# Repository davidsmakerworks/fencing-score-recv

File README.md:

# fencing-score-recv
Remote fencing scoring light display receiver

This is the receiver portion of the [remote fencing scoring light display](https://github.com/davidsmakerworks/fencing-score-xmit) project. This is designed to be placed on the wall at the ends of the fencing strip. It includes a timer to automatically turn off the lights if no shutoff signal is received from the transmitter within a reasonable amount of time.

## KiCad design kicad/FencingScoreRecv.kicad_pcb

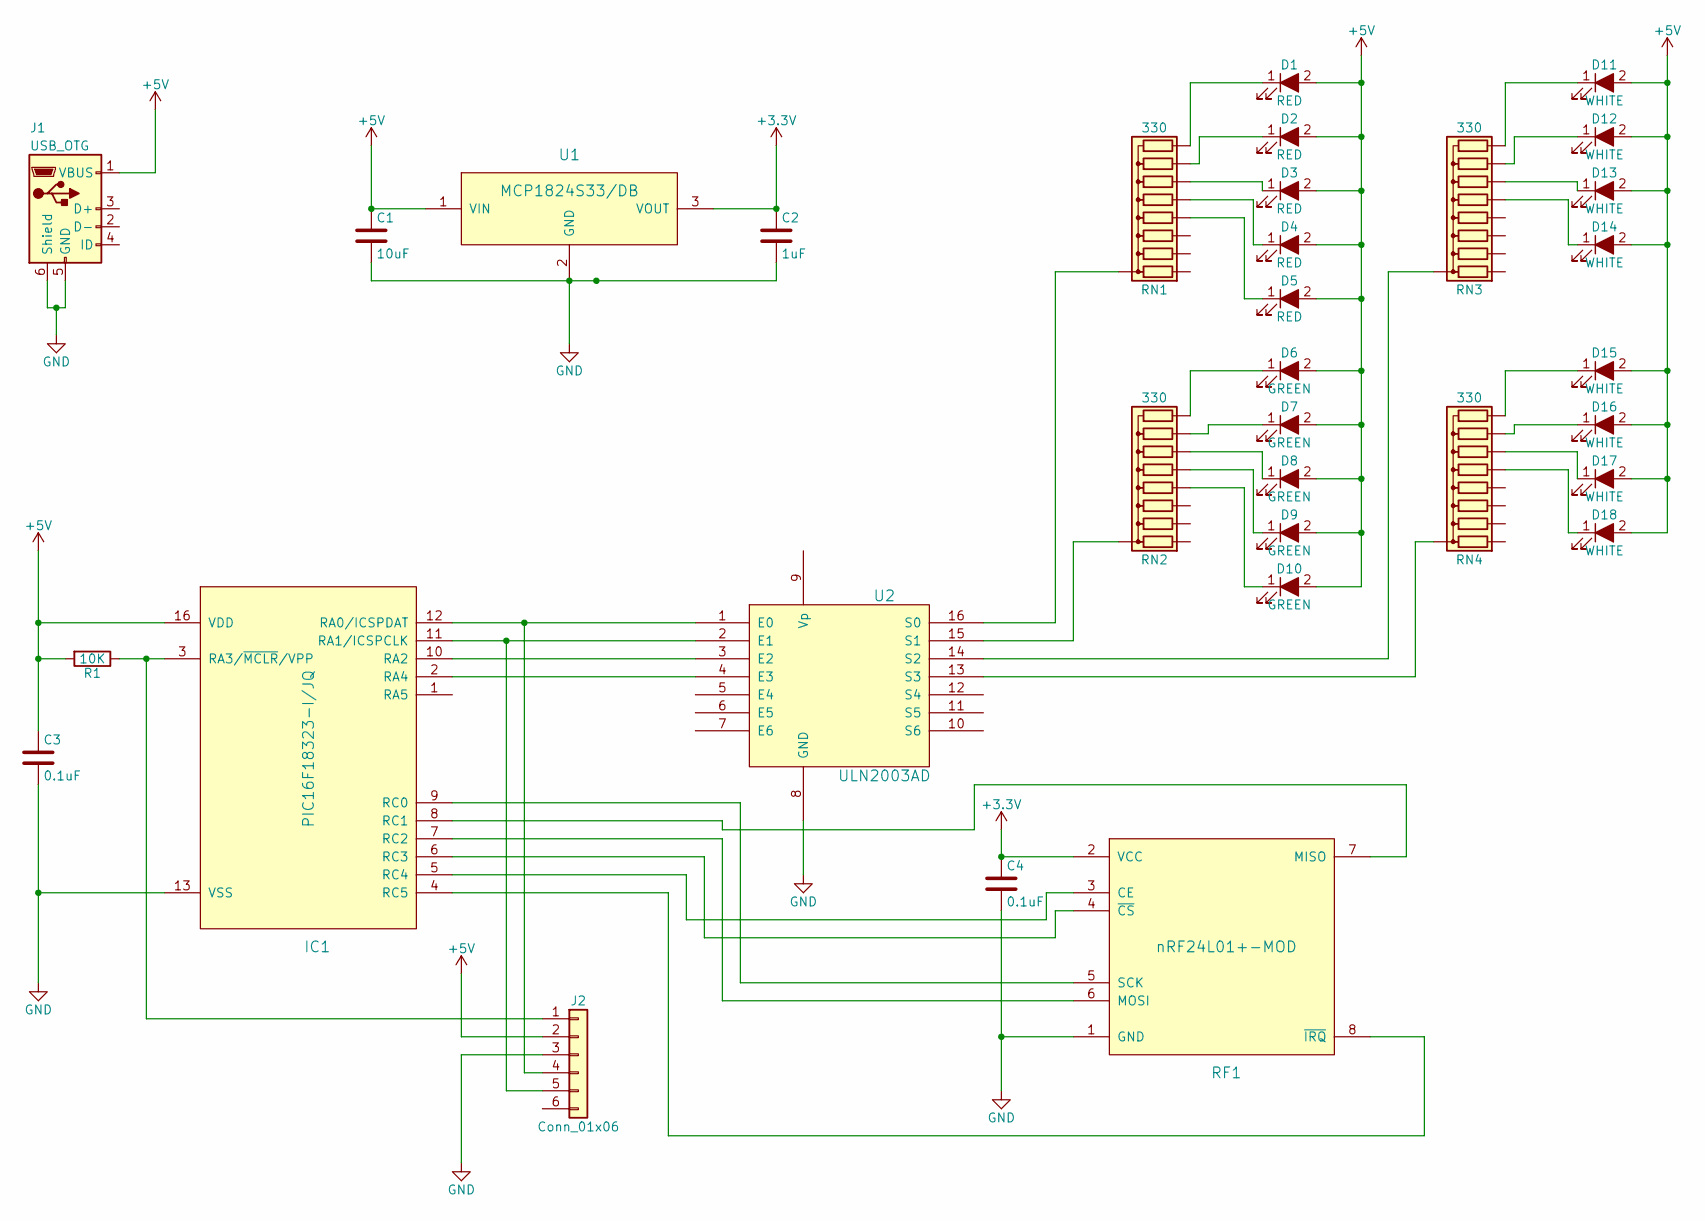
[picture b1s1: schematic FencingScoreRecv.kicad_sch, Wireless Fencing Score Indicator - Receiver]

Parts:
C1: 10uF; C_0805
C2: 1uF; C_0805
C3, C4: 0.1uF; C_0603
D1, D2, D3, D4, D5: RED; LED_D5.0mm
D6, D7, D8, D9, D10: GREEN; LED_D5.0mm
D11, D12, D13, D14, D15, D16, D17, D18: WHITE; LED_D5.0mm
IC1: PIC16F18323-I/JQ; QFN-16-1EP_4x4mm_Pitch0.65mm
J1: USB_OTG; Molex_105164-0001_MicroUSB
J2: Conn_01x06; Pin_Header_Straight_1x06_Pitch2.54mm
R1: 10K; R_0805
RF1: nRF24L01+-MOD; nRF24L01+-Module
RN1, RN2, RN3, RN4: 330; R_Array_SIP9
U1: MCP1824S33/DB; SOT-223
U2: ULN2003AD; SOIC-16_3.9x9.9mm_Pitch1.27mm

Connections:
+3V3: C2.1, C4.1, RF1.2 (VCC), U1.3 (VOUT)
+5V: C1.1, C3.1, D1.2 (A), D2.2 (A), D3.2 (A), D4.2 (A), D5.2 (A), D6.2 (A), D7.2 (A), D8.2 (A), D9.2 (A), D10.2 (A), D11.2 (A), D12.2 (A), D13.2 (A), D14.2 (A), D15.2 (A), D16.2 (A), D17.2 (A), D18.2 (A), IC1.16 (VDD), J1.1 (VBUS), J2.2, R1.2, U1.1 (VIN); also elsewhere on the board
unnamed: D1.1 (K), RN1.9 (R8)
unnamed: D2.1 (K), RN1.8 (R7)
unnamed: D3.1 (K), RN1.7 (R6)
unnamed: D4.1 (K), RN1.6 (R5)
unnamed: D5.1 (K), RN1.5 (R4)
unnamed: D6.1 (K), RN2.9 (R8)
unnamed: D7.1 (K), RN2.8 (R7)
unnamed: D8.1 (K), RN2.7 (R6)
unnamed: D9.1 (K), RN2.6 (R5)
unnamed: D10.1 (K), RN2.5 (R4)
unnamed: D11.1 (K), RN3.9 (R8)
unnamed: D12.1 (K), RN3.8 (R7)
unnamed: D13.1 (K), RN3.7 (R6)
unnamed: D14.1 (K), RN3.6 (R5)
unnamed: D15.1 (K), RN4.9 (R8)
unnamed: D16.1 (K), RN4.8 (R7)
unnamed: D17.1 (K), RN4.7 (R6)
unnamed: D18.1 (K), RN4.6 (R5)
unnamed: IC1.2 (RA4), U2.4 (E3)
unnamed 22: IC1.3 (RA3/~MCLR/VPP), J2.1, R1.1; also elsewhere on the board
unnamed: IC1.4 (RC5), RF1.8 (~IRQ)
unnamed: IC1.5 (RC4), RF1.3 (CE)
unnamed: IC1.6 (RC3), RF1.4 (~CS)
unnamed: IC1.7 (RC2), RF1.6 (MOSI)
unnamed: IC1.8 (RC1), RF1.7 (MISO)
unnamed: IC1.9 (RC0), RF1.5 (SCK)
unnamed: IC1.10 (RA2), U2.3 (E2)
unnamed 30: IC1.11 (RA1/ICSPCLK), J2.5, U2.2 (E1); also elsewhere on the board
unnamed 31: IC1.12 (RA0/ICSPDAT), J2.4, U2.1 (E0); also elsewhere on the board
unnamed: RN1.1 (common), U2.16 (S0)
unnamed: RN2.1 (common), U2.15 (S1)
unnamed: RN3.1 (common), U2.14 (S2)
unnamed: RN4.1 (common), U2.13 (S3)

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
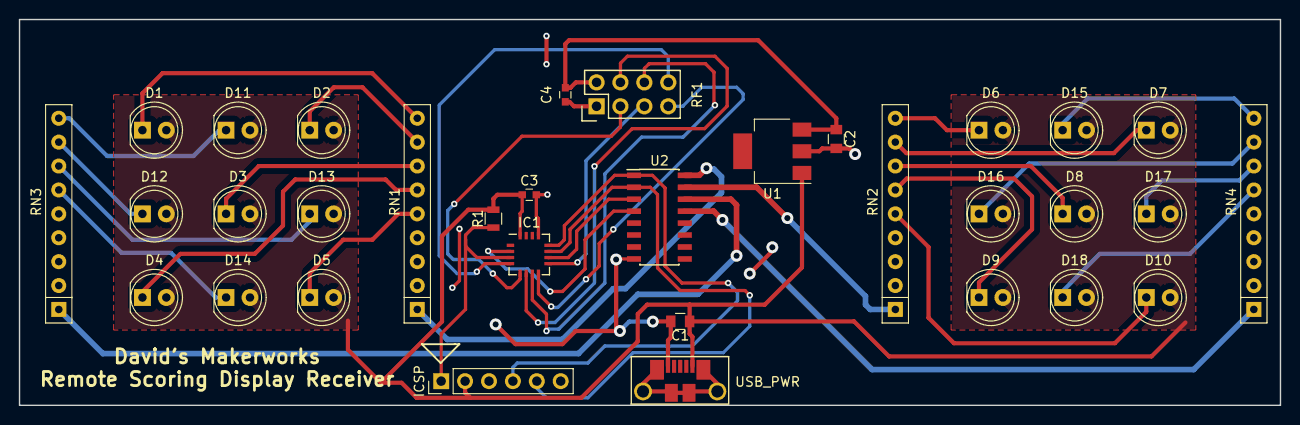
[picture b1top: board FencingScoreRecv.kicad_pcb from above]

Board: 2 copper layers, 134.0 x 41.0 mm, 33 parts (0 on the bottom side), 36 nets.

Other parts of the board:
ICSP: Conn_01x06; Pin_Header_Straight_1x06_Pitch2.54mm
USB_PWR: USB_OTG; Molex_105164-0001_MicroUSB

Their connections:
+5V: ICSP.2, USB_PWR.1; also elsewhere on the board
unnamed 22: ICSP.1; also elsewhere on the board
unnamed 30: ICSP.5; also elsewhere on the board
unnamed 31: ICSP.4; also elsewhere on the board

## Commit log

2019-06-24 Add MIT license
2019-06-24 Fix typo
2019-06-25 Add legacy AVR ASM file from previous version of project
2019-06-26 Update for compatibility with restructured driver
2020-11-16 Update data block
2020-11-16 Internal updates
2020-11-20 Update compiler version
2020-12-25 Remove unnecessary files
2023-03-18 Update RF addr and silkscreen, update for KiCad 7
